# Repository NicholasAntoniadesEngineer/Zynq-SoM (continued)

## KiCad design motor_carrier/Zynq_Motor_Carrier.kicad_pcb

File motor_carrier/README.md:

<!-- schgen:gallery -->
<!-- GENERATED by `schgen gallery` — edits between these markers are overwritten -->
## Generated 3D board views

The placed board rendered from 8 angles by `schgen board` (kicad-cli, the real component 3D models) — regenerated and committed every build, just like the sheets below.

|   |   |   |   |
|---|---|---|---|
| <br>**Perspective (front)** | <br>**Perspective (rear)** | <br>**Top** | <br>**Bottom** |
| <br>**Front edge** | <br>**Back edge** | <br>**Left edge** | <br>**Right edge** |

## Ratsnest views

Placed-board airwires, regenerated by `schgen board`: blue/orange = the subsystem's parts (top/bottom side), steel = SoM, green = intra-subsystem, red = to the SoM. `wired` = in `placement.wired_sheets`.

|   |   |
|---|---|
| <br>**Board (top)** | <br>**Board (bottom)** |
| <br>**SoM region** |   |

|   |   |   |   |
|---|---|---|---|
| <br>**board_control** | <br>**bringup_en** | <br>**can_bus** | <br>**debug_boot** |
| <br>**esc_io** | <br>**esc_power** | <br>**ethernet** | <br>**mechanical** |
| <br>**microsd** | <br>**pd_input** | <br>**power** | <br>**power_mon** |
| <br>**power_som** | <br>**rj45_connector** | <br>**uart_bridge** | <br>**usb_uart_connector** |
| <br>**vbat_supply** |   |   |   |

## Generated schematics

Block diagram and all 21 motor_carrier sheets, regenerated by `schgen board` —
every PNG below passed the netlist, ERC and visual gates.

|   |   |   |
|---|---|---|
| <br>**board_control** | <br>**bringup_en** | <br>**can_bus** |
| <br>**debug_boot** | <br>**esc_io** | <br>**esc_power** |
| <br>**ethernet** | <br>**mechanical** | <br>**microsd** |
| <br>**pd_input** | <br>**power** | <br>**power_mon** |
| <br>**power_som** | <br>**rj45_connector** | <br>**som_decoupling** |
| <br>**som_j1** | <br>**som_j2** | <br>**som_j3** |
| <br>**uart_bridge** | <br>**usb_uart_connector** | <br>**vbat_supply** |

| sheet | description |
|---|---|
| [board_control](renders/board_control.png) | Board control: TCA9535 status expander \| I2C 0x20, rail DIP, user LEDs and button, PUDC strap |
| [bringup_en](renders/bringup_en.png) | Bring-up EN cells: 3x SN74LVC1G08 rail DIP-AND-override |
| [can_bus](renders/can_bus.png) | CAN bus port: TCAN1042HGV transceiver \| switched 120R termination, two daisy-chain connectors |
| [debug_boot](renders/debug_boot.png) | JTAG + SWD headers, boot-request DIP, reset |
| [esc_io](renders/esc_io.png) | 8-channel ESC signal interface \| 5 V PWM/DShot drive, read-back, idle bias, telemetry |
| [esc_power](renders/esc_power.png) | ESC power path: XT60 inlet to outlet \| fuse, reverse/inrush/overcurrent protection, INA237 |
| [ethernet](renders/ethernet.png) | Ethernet: HX5008NL magnetics + Bob-Smith |
| [mechanical](renders/mechanical.png) | Mechanical: M3 mounts + chassis-GND bond (fiducials are PCB-only, emitted by the placer) |
| [microsd](renders/microsd.png) | microSD slot (1.8V SoM <-> 3.3V card, TXS02612) |
| [pd_input](renders/pd_input.png) | Power inlet: USB-C PD 20V/3A + TPS26631 eFuse |
| [power](renders/power.png) | Power: +VIN->+5V->+3V3 bucks + +1V8 LDO, PG LEDs |
| [power_mon](renders/power_mon.png) | Rail telemetry: 2x INA3221 + shunts (I2C 0x40/41) |
| [power_som](renders/power_som.png) | Power: +VIN -> +5V_SOM always-on buck |
| [rj45_connector](renders/rj45_connector.png) | RJ45 8P8C jack (plain, ext. magnetics) |
| [som_decoupling](renders/som_decoupling.png) | SoM power-entry decoupling under the DF40 mezzanine |
| [som_j1](renders/som_j1.png) | SoM J1: power / USB / STM32 / JTAG / SDIO / ETH MDI |
| [som_j2](renders/som_j2.png) | SoM J2: FPGA bank 13/33 IO + VCCO rails |
| [som_j3](renders/som_j3.png) | SoM J3: FPGA bank 33/34/35 IO + VCCO rails |
| [uart_bridge](renders/uart_bridge.png) | UART bridge: CP2102N USB-UART |
| [usb_uart_connector](renders/usb_uart_connector.png) | USB-C UFP console port -> CP2102N |
| [vbat_supply](renders/vbat_supply.png) | Battery logic feed: TPS26631 eFuse \| LM61460 8 V pre-regulator, supply selector |
<!-- /schgen:gallery -->

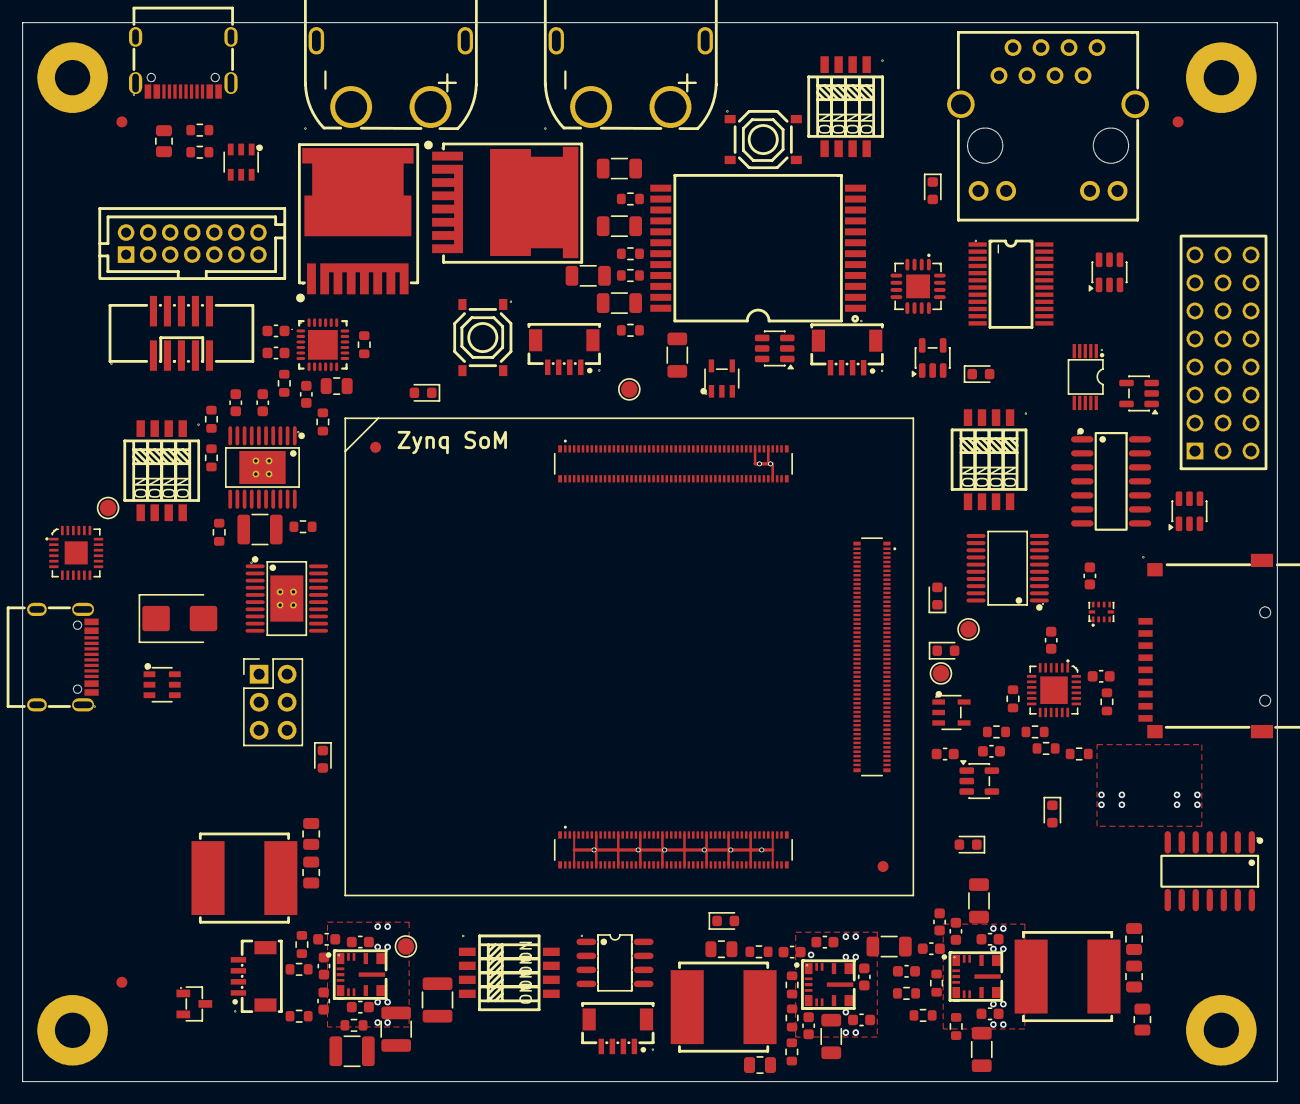
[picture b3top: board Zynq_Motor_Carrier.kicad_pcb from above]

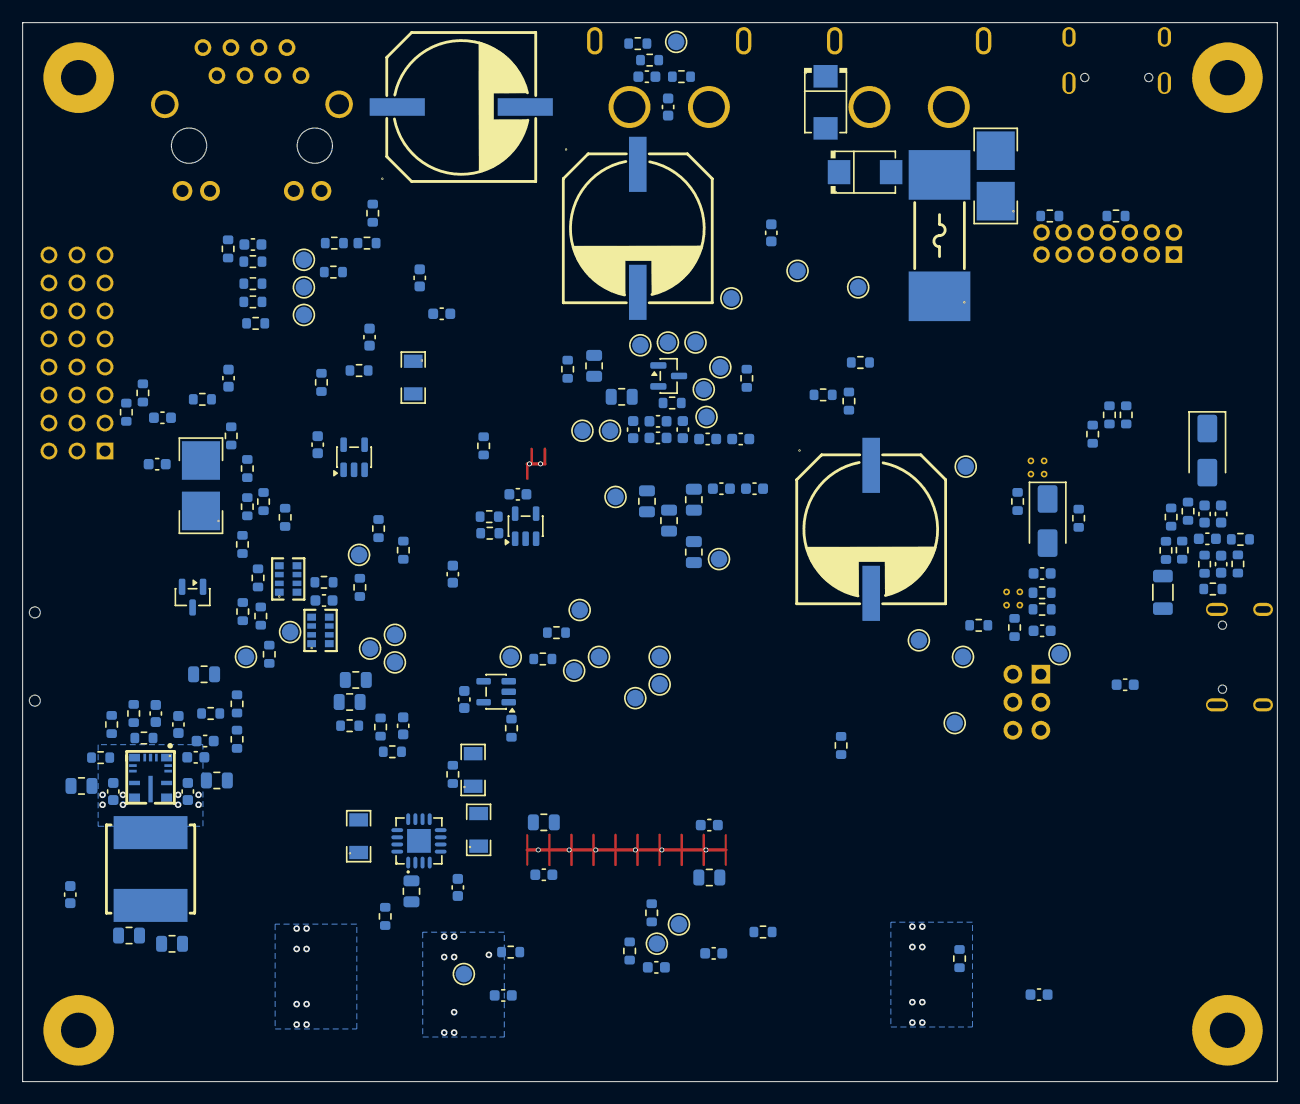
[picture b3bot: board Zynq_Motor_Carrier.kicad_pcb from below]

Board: 6 copper layers, 113.8 x 96.0 mm, 363 parts (204 on the bottom side), 233 nets.

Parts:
C1001, C2001, C2002, C2003, C3001, C3002, C5001, C5004, C5005, C5006, C5007, C6002, C6010, C7006, C9001, C9002, C9004, C10001, C10004, C11001, C11004, C11007, C11009, C11025, C11029, C12001, C12002, C13014, C13017, C13025, C15003, C15004, C15005, C15006, C15009, C15010, C15011, C15012, C15015, C15016, C15017, C15018, C19001, C19003, C19004, C21009: 100n; C_0603_1608Metric
C1002, C1003, C5002, C5003, C12003, C19002, C20001: 10u; C_0805_2012Metric
C6001, C6005, C6006, C6011, C21002, C21005, C21006: 100n/100V; C_0603_1608Metric
C6003, C6004, C21014: 470u; RVT1H471M1213
C6007, C6009, C11012, C11013, C11024, C11028, C11031, C11032, C13022, C13023, C21007, C21008: 1u; C_0603_1608Metric
C6008: 1u/100V; C_1206_3216Metric
C7001, C7002, C7003, C7004, C7005: 1n; C_1206_3216Metric
C9003, C11005, C11006, C11008, C11010, C11011, C11026, C11030, C13018, C13019, C15001, C15002, C15007, C15008, C15013, C15014, C21010, C21011: 22u; C_0805_2012Metric
C10002: 10u; C_1210_3225Metric
C10003, C21001: 47n; C_0603_1608Metric
C11002, C11003, C13015, C13016: 10u; C_1206_3216Metric
C11023, C11027, C13021, C21012: 22p; C_0603_1608Metric
C21003, C21004, C21013: 4u7/100V; C_1210_3225Metric
D1001: green; LED_0603_1608Metric
D1002, D6004, D11001, D11002, D11003, D13004, D21001: red; LED_0603_1608Metric
D3001: NUP2105LT1G
D5001, D5002, D5003: SRV05-4; SOT-23-6
D5004: blue; LED_0603_1608Metric
D6001, D6002: SMBJ28A
D6003, D21002: SS54; D_SMA
D10001: SMBJ22A; D_SMB
F6001: 40A; 0456040.DR
FID1, FID2, FID3, FID4, FID5: Fiducial; Fiducial_1mm_Mask2mm
H8001, H8002, H8003, H8004: MountingHole_M3; MountingHole_3.2mm_M3_Pad
J1001, J3001, J3002, J5002: ZX-SH1.0-4PLT
J4001: 878311420
J4002: HX_JN1.27-2x5; HX_JN1.27-2x5_TP_H4.9
J5001: HX PZ2.54-3x8P ZZ; HX_PZ2.54-3x8P_ZZ
J6001, J6002: XT60PW-M
J9001: TF-01A
J10001, J20001: TYPE-C-31-M-12
J14001: KH-5224-8P8C-D
J16001, J17002, J18003: DF40C-100DP-0.4V(51); HRS_DF40C-100DP-0.4V_51_
J21001: A2541WV-2x3P; PinHeader_2x03_P2.54mm_Vertical
L11001, L11002, L13003, L21001: 10uH; SWPA8040S100MT
Q1001, Q11001: AO3400A; SOT-23
Q6001, Q6002: IPT007N06N
R1001, R1002, R4001, R4002, R6006, R6008: 4k7; R_0603_1608Metric
R1003, R1007, R1012, R3001, R4004, R4005, R4006, R5001, R5004, R5005, R5006, R5007, R5008, R5009, R5010, R5011, R5014, R5015, R6001, R6009, R6010, R6013, R6014, R9006, R11002, R11005, R12001, R21002: 10k; R_0603_1608Metric
R1004, R1009, R1011, R2001, R2002, R2003, R2004, R2005, R2006, R5003, R5012, R6011, R6012, R9001, R9002, R9003, R9004, R9005, R10003, R10006, R11008, R21001, R21005: 100k; R_0603_1608Metric
R1005, R1006, R1008, R1013, R5013, R5016, R11003, R11007, R11012, R11015, R13016, R13019, R19001, R21010, R21011: 1k; R_0603_1608Metric
R1010, R5002, R13015: 13k; R_0603_1608Metric
R3002: 120R; R_0603_1608Metric
R4003, R6004: 100R; R_0603_1608Metric
R6002, R6003, R10005, R20001, R20002, R21003: 5.1k; R_0603_1608Metric
R6005: 49.9R; R_0603_1608Metric
R6007: 15k; R_0603_1608Metric
R7001, R7002, R7003, R7004: 75R; R_0603_1608Metric
R10004, R21004: 5.49k; R_0603_1608Metric
R11001: 40.2k; R_0603_1608Metric
R11004: 23.2k; R_0603_1608Metric
R11006, R11009, R14001, R14002: 330R; R_0603_1608Metric
R11010, R11014, R13018, R21007: 22k; R_0603_1608Metric
R11011, R11013, R13017, R21006: 10R; R_0603_1608Metric
R13014, R19003, R21008: 47k5; R_0603_1608Metric
R19002: 22k1; R_0603_1608Metric
R21009: 6.8k; R_0603_1608Metric
RN5001, RN5002: 4D03WGJ0330T5E
RS6001: 0.5mR; RLM25FEGMR50M
RS12001, RS12002, RS12003: 10mR; RLM12FTCMR010
RS12004: 20mR; RLM12FTCMR020
RT6001: 0.5mR; RLM25FEGMR50M
SW1001, SW3001, SW4001, SW5001: DIP-4; DSHP04TSGER
SW1002: USER; TS-1187A-B-A-B
SW4002: RESET; TS-1187A-B-A-B
T7001: HX5008NLT
TP1001: XP16; TestPoint_Pad_D1.5mm
TP1002: XP17; TestPoint_Pad_D1.5mm
TP1005: STM32_I2C2_SCL; TestPoint_Pad_D1.5mm
TP1006: STM32_I2C2_SDA; TestPoint_Pad_D1.5mm
TP1007: +3V3_SC; TestPoint_Pad_D1.5mm
TP1008: SC_INT_N; TestPoint_Pad_D1.5mm
TP1009: PUDC_34; TestPoint_Pad_D1.5mm
TP1010: +5V_FAN; TestPoint_Pad_D1.5mm
TP1011: ESC_PWR_REQ; TestPoint_Pad_D1.5mm
TP2001: EN_5V0; TestPoint_Pad_D1.5mm
TP2002: EN_3V3; TestPoint_Pad_D1.5mm
TP2003: EN_1V8; TestPoint_Pad_D1.5mm
TP3001: CAN_H; TestPoint_Pad_D1.5mm
TP3002: CAN_L; TestPoint_Pad_D1.5mm
TP4001: VBUS_OUT_EN; TestPoint_Pad_D1.5mm
TP5001: +5V_MOTOR_IO; TestPoint_Pad_D1.5mm
TP5002: ESC_BIAS; TestPoint_Pad_D1.5mm
TP5003: OE_BUF_N; TestPoint_Pad_D1.5mm
TP6001: +VESC_IN; TestPoint_Pad_D1.5mm
TP6002: +VESC; TestPoint_Pad_D1.5mm
TP6003: GND_MOTOR; TestPoint_Pad_D1.5mm
TP6004, TP11004: GND; TestPoint_Pad_D1.5mm
TP6005: +VESC_F; TestPoint_Pad_D1.5mm
TP6006: +VESC_MID; TestPoint_Pad_D1.5mm
TP6007: +VESC_P; TestPoint_Pad_D1.5mm
TP6008: ESC_PWR_EN; TestPoint_Pad_D1.5mm
TP6009: PROT_IMON; TestPoint_Pad_D1.5mm
TP6010: VSENSE_DIV; TestPoint_Pad_D1.5mm
TP9001: SDIO_CMD; TestPoint_Pad_D1.5mm
TP9002: SDIO_CLK; TestPoint_Pad_D1.5mm
TP10001: +VBUS_IN; TestPoint_Pad_D1.5mm
TP10002: +VIN_PD; TestPoint_Pad_D1.5mm
TP11001: +5V; TestPoint_Pad_D1.5mm
TP11002: +3V3; TestPoint_Pad_D1.5mm
TP11003: +1V8; TestPoint_Pad_D1.5mm
TP13001: +5V_SOM; TestPoint_Pad_D1.5mm
TP19001: ZYNQ_PS_UART0_TXD; TestPoint_Pad_D1.5mm
TP19002: ZYNQ_PS_UART0_RXD; TestPoint_Pad_D1.5mm
TP21001: +VBAT_SW; TestPoint_Pad_D1.5mm
TP21002: +VPRE; TestPoint_Pad_D1.5mm
TP21003: +VIN; TestPoint_Pad_D1.5mm
TP21004: +VBAT_D; TestPoint_Pad_D1.5mm
U1001: TCA9535PWR
U1002, U5003: SY6280AAC
U2001, U2002, U2003, U5006, U5007: SN74LVC1G08; SOT-23-5
U3001: TCAN1042HGVDR
U5001: SN74HCT245PWR
U5004, U5005: SN74LVC125ADR
U6001: INA237AIDGSR
U6002: LM74930QRGERQ1
U9001: TXS02612RTWR
U9002: TPD6E001RSER
U10001, U21001: TPS26631PWPR
U10002, U20001: USBLC6-2SC6
U11001, U11002, U13004, U21002: LM61460AANRJRR
U11003: AP2112K-1.8; SOT-23-5
U12001, U12002: INA3221AIRGVR
U19001: CP2102N-A02; CP2102N-A02-GQFN24R

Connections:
+1V8: C9001.1, R11007.1, RS12004.2, TP11003.1, U9001.5, U12002.11
+1V8_REG: C11013.1, RS12004.1, U11003.5, U12002.12
+3V3: C3002.1, C5004.1, C5005.1, C5006.1, C5007.1, C9002.1, C9003.1, C9004.1, C11012.1, C15007.1, C15008.1, C15009.1, C15010.1, C15011.1, C15012.1, C19001.1, C19002.1, C19003.1, C19004.1, D11003.2, J4001.2, J9001.4, J17002.1, J17002.2, J17002.3, J17002.98, J17002.99, J17002.100, J18003.1, J18003.2, J18003.4, J18003.97, J18003.99, R1008.1, R1012.1, R3001.1, R4001.1, R4002.1, R5014.1, R9001.1, R9002.1, R9003.1, R9004.1, R9005.1, R9006.1, R14001.1, R14002.1, R19001.1, RS12003.2, TP11002.1, U3001.5, U5004.14, U5005.14, U5006.2, U5006.5, U5007.2, U5007.5, U9001.17, U9001.21, U9002.10, U11003.1, U12001.1, U19001.5, U19001.6, U19001.7
+3V3_REG: C11010.1, C11011.1, C11023.1, D11002.2, L11002.2, R11004.1, R11013.1, RS12003.1, U12001.2
+3V3_SC: C1001.1, C2001.1, C2002.1, C2003.1, C6002.1, C10004.1, C12001.1, C12002.1, C12003.1, C15013.1, C15014.1, C15015.1, C15016.1, C15017.1, C15018.1, J4002.1, J16001.37, R1001.1, R1002.1, R1003.1, R1005.1, R1006.1, R1007.1, R2002.1, R2004.1, R2006.1, R4003.1, R4004.1, R4005.1, R4006.1, R6001.1, R6010.1, R10006.1, R12001.1, R21005.1, SW1001.5, SW1001.6, SW1001.7, SW1001.8, TP1007.1, U1001.24, U2001.5, U2002.5, U2003.5, U6001.1, U6001.6, U10002.5, U12001.4, U12001.16, U12002.4, U12002.5, U12002.16
+5V: C1002.1, C3001.1, C5001.1, C5002.1, C11007.1, C11008.1, C11029.1, C11030.1, D5001.5, D5002.5, D5003.5, R5001.1, R5016.1, RS12002.2, SW5001.7, TP11001.1, U1002.4, U1002.5, U3001.3, U5001.1, U5001.20, U5003.5, U11002.8, U11002.12, U12001.14
+5V_FAN: C1003.1, J1001.2, TP1010.1, U1002.1
+5V_MOTOR_IO: C5003.1, J5001.9, J5001.10, J5001.11, J5001.12, J5001.13, J5001.14, J5001.15, J5001.16, TP5001.1, U5003.1
+5V_REG: C11005.1, C11006.1, C11026.1, C11027.1, D11001.2, L11001.2, R11001.1, R11011.1, RS12002.1, U12001.15
+5V_SOM: C13018.1, C13019.1, C13021.1, C15001.1, C15002.1, C15003.1, C15004.1, C15005.1, C15006.1, D13004.2, J16001.1, J16001.2, J16001.3, J16001.4, J16001.5, J16001.6, J16001.7, J16001.8, J16001.9, J16001.10, J16001.11, J16001.12, J16001.13, J16001.14, L13003.2, R13014.1, R13017.1, TP13001.1
+VBAT_D: C21002.1, D21002.1, R21001.1, TP21004.1, U21001.1, U21001.2, U21001.3, U21001.6
+VBAT_SW: C21003.1, C21004.1, C21005.1, C21006.1, C21013.1, C21014.1, TP21001.1, U21001.18, U21001.19, U21001.20, U21002.7, U21002.8, U21002.12
+VBUS_IN: C10001.1, D10001.1, J10001.A4B9, J10001.B4A9, R10003.1, TP10001.1, U10001.1, U10001.2, U10001.3, U10001.6, U10001.7
+VESC: C6003.1, C6004.1, C6005.1, D6004.2, J6002.2, R6012.1, RS6001.2, TP6002.1, U6001.8, U6001.9, U6002.19
+VESC_F: C6001.1, D6001.1, D6003.2, D21002.2, F6001.2, Q6001.3, TP6005.1
+VESC_IN: F6001.1, J6001.2, TP6001.1
+VESC_MID: Q6001.2, Q6002.2, TP6006.1, U6002.2, U6002.15
+VESC_P: C6006.1, Q6002.3, R6005.1, R6006.1, RS6001.1, TP6007.1, U6001.10, U6002.24
+VIN: J21001.3, J21001.4, RS12001.1, TP21003.1, U12001.12
+VIN_PD: C10002.1, J21001.1, J21001.2, TP10002.1, U10001.18, U10001.19, U10001.20
+VIN_SYS: C11001.1, C11002.1, C11003.1, C11025.1, C13014.1, C13015.1, C13016.1, C13025.1, RS12001.2, U11001.8, U11001.12, U12001.11, U13004.7, U13004.8, U13004.12
+VPRE: C21010.1, C21011.1, C21012.1, D21001.2, J21001.5, J21001.6, L21001.2, R21006.1, R21008.1, TP21002.1
/board_control/BTN_N: R1007.2, SW1002.1, SW1002.2, U1001.16
/board_control/DIP_USER: R1004.1, SW1001.4, U1001.13
/board_control/FAN_PWM_OD: J1001.4, Q1001.3
/board_control/XP16: TP1001.1, U1001.19
/board_control/XP17: TP1002.1, U1001.20
/can_bus/CAN_H: D3001.1, J3001.2, J3002.2, R3002.1, TP3001.1, U3001.7
/can_bus/CAN_L: D3001.2, J3001.3, J3002.3, SW3001.8, TP3002.1, U3001.6
/can_bus/CAN_TERM: R3002.2, SW3001.1
/esc_io/ESC_BIAS: R5004.2, R5005.2, R5006.2, R5007.2, R5008.2, R5009.2, R5010.2, R5011.2, TP5002.1, U5006.4
/esc_io/ESC_OUT0: D5001.1, J5001.1, R5004.1, RN5001.8
/esc_io/ESC_OUT1: D5001.3, J5001.2, R5005.1, RN5001.7
/esc_io/ESC_OUT2: D5001.4, J5001.3, R5006.1, RN5001.6
/esc_io/ESC_OUT3: D5001.6, J5001.4, R5007.1, RN5001.5
/esc_io/ESC_OUT4: D5002.1, J5001.5, R5008.1, RN5002.8
/esc_io/ESC_OUT5: D5002.3, J5001.6, R5009.1, RN5002.7
/esc_io/ESC_OUT6: D5002.4, J5001.7, R5010.1, RN5002.6
/esc_io/ESC_OUT7: D5002.6, J5001.8, R5011.1, RN5002.5
/esc_io/ESC_SIG0: RN5001.1, U5001.18, U5004.2
/esc_io/ESC_SIG1: RN5001.2, U5001.17, U5004.5
/esc_io/ESC_SIG2: RN5001.3, U5001.16, U5004.9
/esc_io/ESC_SIG3: RN5001.4, U5001.15, U5004.12
/esc_io/ESC_SIG4: RN5002.1, U5001.14, U5005.2
/esc_io/ESC_SIG5: RN5002.2, U5001.13, U5005.5
/esc_io/ESC_SIG6: RN5002.3, U5001.12, U5005.9
/esc_io/ESC_SIG7: RN5002.4, U5001.11, U5005.12
/esc_io/OE_BUF_N: D5004.1, R5001.2, R5015.1, SW5001.8, TP5003.1, U5001.19
/esc_io/SERVO_SW_EN: R5003.1, SW5001.2, U5003.4
/esc_io/TLM_CONN: D5003.1, J5002.2, R5013.1
/esc_power/PROT_DGATE: Q6002.1, U6002.1
/esc_power/PROT_HGATE: Q6001.1, R6004.1, U6002.14
/esc_power/PROT_IMON: R6008.1, R6009.1, TP6009.1, U6002.10
/esc_power/PROT_VS: C6007.2, C6011.1, D6003.1, U6002.4, U6002.7, U6002.22
/esc_power/VSENSE_DIV: C6010.1, R6012.2, R6013.1, R6014.1, TP6010.1
/ethernet/BS_COMMON: C7001.2, C7002.2, C7003.2, C7004.2, C7005.1, R7001.2, R7002.2, R7003.2, R7004.2
/ethernet/ETH_TCT: C7006.1, T7001.1, T7001.4, T7001.7, T7001.10
/ethernet/MCT1: C7001.1, R7001.1, T7001.24
/ethernet/MCT2: C7002.1, R7002.1, T7001.21
/ethernet/MCT3: C7003.1, R7003.1, T7001.18
/ethernet/MCT4: C7004.1, R7004.1, T7001.15
/microsd/SD_CARD_CLK: J9001.5, U9001.19, U9002.1
/microsd/SD_CARD_CMD: J9001.3, R9001.2, U9001.20, U9002.2
/microsd/SD_CARD_D0: J9001.7, R9002.2, U9001.18, U9002.3
/microsd/SD_CARD_D1: J9001.8, R9003.2, U9001.16, U9002.6
/microsd/SD_CARD_D2: J9001.1, R9004.2, U9001.23, U9002.7
/microsd/SD_CARD_D3: J9001.2, R9005.2, U9001.22, U9002.8
/pd_input/PD_USB_DN_CONN: J10001.A7, J10001.B7, U10002.3
/pd_input/PD_USB_DP_CONN: J10001.A6, J10001.B6, U10002.1
/power/BIAS_3V3: C11032.1, R11013.2, U11002.1
/power/BIAS_5V0: C11028.1, R11011.2, U11001.1
/power/RT_3V3: R11014.1, U11002.6
/power/RT_5V0: R11010.1, U11001.6
/power_som/BIAS_5V_SOM: C13023.1, R13017.2, U13004.1
/power_som/RT_5V_SOM: R13018.1, U13004.6
/uart_bridge/CP2102N_VBUS_SNS: R19002.2, R19003.1, U19001.8
/usb_uart_connector/USB_UART_DM_CONN: J20001.A7, J20001.B7, U20001.3
/usb_uart_connector/USB_UART_DP_CONN: J20001.A6, J20001.B6, U20001.1
/vbat_supply/BIAS_PRE: C21008.1, R21006.2, U21002.1
/vbat_supply/RT_PRE: R21007.1, U21002.6
BU_DIP_1V8: R2005.1, SW1001.3, U1001.11, U2003.1
BU_DIP_3V3: R2003.1, SW1001.2, U1001.10, U2002.1
BU_DIP_5V0: R2001.1, SW1001.1, U1001.9, U2001.1
CAN_RX: J17002.54, U3001.4
CAN_TX: J17002.77, R3001.2, U3001.1
CHASSIS_GND: C7005.2, H8001.1, H8002.1, H8003.1, H8004.1, J10001.1, J10001.2, J10001.3, J10001.4, J14001.13, J20001.1, J20001.2, J20001.3, J20001.4
EN_1V8: TP2003.1, U2003.4, U11003.3
EN_3V3: TP2002.1, U2002.4, U11002.7
EN_5V0: TP2001.1, U2001.4, U11001.7
ESC_BUF_OE_N: J17002.57, SW5001.1
ESC_BUF_OE_SENSE_N: R5015.2, U1001.8
ESC_FAULT_N: J17002.37, R6001.2, U1001.7, U6001.3
ESC_FB0: J17002.82, U5004.3
ESC_FB1: J17002.84, U5004.6
ESC_FB2: J17002.78, U5004.8
ESC_FB3: J17002.80, U5004.11
ESC_FB4: J17002.92, U5005.3
ESC_FB5: J17002.94, U5005.6
ESC_FB6: J17002.90, U5005.8
ESC_FB7: J17002.88, U5005.11
ESC_IDLE_SEL: J17002.87, R5012.1, U5006.1
ESC_IMON: J16001.92, R6009.2
ESC_PWM_IN0: J17002.81, U5001.2
ESC_PWM_IN1: J17002.83, U5001.3
ESC_PWM_IN2: J17002.93, U5001.4
ESC_PWM_IN3: J17002.91, U5001.5
ESC_PWM_IN4: J18003.91, U5001.6
ESC_PWM_IN5: J18003.93, U5001.7
ESC_PWM_IN6: J18003.92, U5001.8
ESC_PWM_IN7: J18003.94, U5001.9
ESC_PWR_EN: R6011.1, SW5001.6, TP6008.1, U6002.6
ESC_PWR_FLT_N: R6010.2, U1001.18, U6002.12
ESC_PWR_REQ: R1009.1, SW5001.3, TP1011.1, U1001.17
ESC_TLM_RX: J17002.89, U5007.4
ESC_VBAT_SENSE: J16001.74, R6014.2
ETH_LINE_MDI_0_N: J14001.2, T7001.22
ETH_LINE_MDI_0_P: J14001.1, T7001.23
ETH_LINE_MDI_1_N: J14001.6, T7001.19
ETH_LINE_MDI_1_P: J14001.3, T7001.20
ETH_LINE_MDI_2_N: J14001.5, T7001.16
ETH_LINE_MDI_2_P: J14001.4, T7001.17
ETH_LINE_MDI_3_N: J14001.8, T7001.13
ETH_LINE_MDI_3_P: J14001.7, T7001.14
ETH_PHY_MDI0_N: J16001.95, T7001.3
ETH_PHY_MDI0_P: J16001.97, T7001.2
ETH_PHY_MDI1_N: J16001.89, T7001.6
ETH_PHY_MDI1_P: J16001.91, T7001.5
ETH_PHY_MDI2_N: J16001.83, T7001.9
ETH_PHY_MDI2_P: J16001.85, T7001.8
ETH_PHY_MDI3_N: J16001.77, T7001.12
ETH_PHY_MDI3_P: J16001.79, T7001.11
FAN_PWM: J17002.59, Q1001.1, R1011.1
FAN_TACH: J17002.44, R1012.2, R1013.2
GND: C1001.2, C1002.2, C1003.2, C2001.2, C2002.2, C2003.2, C3001.2, C3002.2, C5001.2, C5002.2, C5003.2, C5004.2, C5005.2, C5006.2, C5007.2, C6002.2, C6010.2, C7006.2, C9001.2, C9002.2, C9003.2, C9004.2, C10001.2, C10002.2, C10003.2, C10004.2, C11001.2, C11002.2, C11003.2, C11005.2, C11006.2, C11007.2, C11008.2, C11010.2, C11011.2, C11012.2, C11013.2, C11024.2, C11025.2, C11026.2, C11028.2, C11029.2, C11030.2, C11031.2, C11032.2, C12001.2, C12002.2, C12003.2, C13014.2, C13015.2, C13016.2, C13018.2, C13019.2, C13022.2, C13023.2, C13025.2, C15001.2, C15002.2, C15003.2, C15004.2, C15005.2, C15006.2, C15007.2, C15008.2, C15009.2, C15010.2, C15011.2, C15012.2, C15013.2, C15014.2, C15015.2, C15016.2, C15017.2, C15018.2, C19001.2, C19002.2, C19003.2, C19004.2, C20001.2, C21001.2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
GND_MOTOR: C6001.2, C6003.2, C6004.2, C6005.2, C6006.2, C6008.2, C6009.2, C6011.2, D3001.3, D5001.2, D5002.2, D5003.2, D6002.1, J3001.4, J3001.5, J3001.6, J3002.4, J3002.5, J3002.6, J5001.17, J5001.18, J5001.19, J5001.20, J5001.21, J5001.22, J5001.23, J5001.24, J5002.1, J5002.5, J5002.6, J6001.1, J6001.3, J6001.4, J6002.1, J6002.3, J6002.4, R6003.2, R6007.2, R6008.2, R6011.2, RT6001.1, TP6003.1, U6002.5, U6002.13, U6002.16
unnamed: C6008.1, R6004.2
unnamed: C11023.2, R11015.1
unnamed: C11027.2, R11012.1
unnamed: C13021.2, R13019.1
unnamed: C21012.2, R21010.1
unnamed: D1001.2, R1005.2
unnamed: D1001.1, U1001.14
unnamed: D1002.2, R1006.2
unnamed: D1002.1, U1001.15
unnamed: D5004.2, R5016.2
unnamed: D6001.2, D6002.2
unnamed: D6004.1, R6002.1
unnamed: D11001.1, R11003.1
unnamed: D11002.1, R11006.1
unnamed: D11003.1, R11009.1
unnamed: D13004.1, R13016.1
unnamed: D21001.1, R21011.1
unnamed: J1001.3, R1013.1
unnamed: J14001.9, R14001.2
unnamed: J14001.11, R14002.2
unnamed: J20001.A5, R20001.1
unnamed: J20001.B5, R20002.1
unnamed: Q11001.3, R11009.2
unnamed: Q11001.1, R11007.2, R11008.1
unnamed: R4003.2, SW4001.8
unnamed: R4006.2, SW4001.4
unnamed: R5013.2, R5014.2, U5007.1
unnamed: R6002.2, R6003.1
unnamed: R1010.1, U1002.3
unnamed: R5002.1, U5003.3
unnamed: C6007.1, U6002.23
unnamed: R6005.2, U6002.20
unnamed: R6007.1, U6002.11
unnamed: R6006.2, U6002.18
unnamed: C6009.1, U6002.9
unnamed: R10005.1, U10001.11
unnamed: R10003.2, R10004.1, U10001.8
unnamed: C10003.1, U10001.10
unnamed: C11004.1, U11001.13, U11001.14
unnamed: R11001.2, R11002.1, R11012.2, U11001.4
unnamed: C11004.2, L11001.1, U11001.10
unnamed: C11024.1, U11001.2
unnamed: C11009.1, U11002.13, U11002.14
unnamed: R11004.2, R11005.1, R11015.2, U11002.4
unnamed: C11009.2, L11002.1, U11002.10
unnamed: C11031.1, U11002.2
unnamed: C13017.1, U13004.13, U13004.14
unnamed: R13014.2, R13015.1, R13019.2, U13004.4
unnamed: C13017.2, L13003.1, U13004.10
unnamed: C13022.1, U13004.2
unnamed: R19001.2, U19001.9
unnamed: R21004.1, U21001.11
unnamed: R21002.2, R21003.1, U21001.8
unnamed: R21001.2, R21002.1, U21001.7
unnamed: C21001.1, U21001.10
unnamed: C21009.1, U21002.13, U21002.14
unnamed: R21008.2, R21009.1, R21010.2, U21002.4
unnamed: C21009.2, L21001.1, U21002.10
unnamed: C21007.1, U21002.2
PD_FLT_N: R10006.2, U1001.4, U10001.15
PMON_ALERT_N: R12001.2, U1001.5, U12001.9, U12002.9
PUDC_34: J18003.39, R1008.2, TP1009.1
SC_INT_N: J16001.41, R1003.2, TP1008.1, U1001.1
SDIO_CLK: J16001.67, TP9002.1, U9001.9
SDIO_CMD: J16001.69, TP9001.1, U9001.4
SDIO_D0: J16001.65, U9001.6
SDIO_D1: J16001.61, U9001.7
SDIO_D2: J16001.73, U9001.1
SDIO_D3: J16001.71, U9001.3
SD_CARD_DETECT: J9001.9, J17002.17, R9006.2
STM32_BOOT0: J16001.57, SW4001.1
STM32_GPIO5: J4002.4, J16001.53
STM32_GPIO6: J4002.2, J16001.45
STM32_GPIO7: J16001.59, R4004.2, SW4001.2
STM32_GPIO8: J16001.54, R4005.2, SW4001.3
STM32_I2C2_SCL: J16001.55, R1001.2, TP1005.1, U1001.22, U6001.5, U12001.6, U12002.6
STM32_I2C2_SDA: J16001.49, R1002.2, TP1006.1, U1001.23, U6001.4, U12001.7, U12002.7
STM32_NRST: J4002.10, J16001.47, SW4002.1, SW4002.2
STM32_RAIL_EN_1V8: J16001.43, R2006.2, U2003.2
STM32_RAIL_EN_3V3: J16001.35, R2004.2, U2002.2
STM32_RAIL_EN_5V0: J16001.33, R2002.2, U2001.2
STM32_USB_CC1: J10001.A5, J16001.29
STM32_USB_CC2: J10001.B5, J16001.31
STM32_USB_D_N: J16001.21, U10002.4
STM32_USB_D_P: J16001.19, U10002.6
USB_UART_DM: U19001.4, U20001.4
USB_UART_DP: U19001.3, U20001.6
USB_UART_VBUS: C20001.1, J20001.A4B9, J20001.B4A9, R19002.1, U20001.5
VBAT_FLT_N: R21005.2, U1001.6, U21001.15
VBUS_OUT_EN: J16001.38, TP4001.1
ZYNQ_PS_UART0_CTS_N: J17002.11, U19001.19
ZYNQ_PS_UART0_RTS_N: J17002.8, U19001.18
ZYNQ_PS_UART0_RXD: J16001.42, TP19002.1, U19001.21
ZYNQ_PS_UART0_TXD: J16001.48, TP19001.1, U19001.20
ZYNQ_TCK: J4001.6, J16001.64
ZYNQ_TDI: J4001.10, J16001.70, R4002.2
ZYNQ_TDO: J4001.8, J16001.68
ZYNQ_TMS: J4001.4, J16001.66, R4001.2

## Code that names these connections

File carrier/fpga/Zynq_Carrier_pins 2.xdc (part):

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##############################################################################

# ---- bank 13 — VCCO = +3V3 (43 pins) --------------------
set_property -dict {PACKAGE_PIN AA9  IOSTANDARD LVCMOS33} [get_ports {DBG_UART_RXD}]  ;# J2.42 IO_L11P_T1_SRCC_13 <- usb_jtag
#   ^ SRCC-capable: # create_clock -name DBG_UART_RXD -period <ns> [get_ports {DBG_UART_RXD}]
set_property -dict {PACKAGE_PIN AA8  IOSTANDARD LVCMOS33} [get_ports {DBG_UART_TXD}]  ;# J2.40 IO_L11N_T1_SRCC_13 <- usb_jtag
set_property -dict {PACKAGE_PIN V10  IOSTANDARD LVCMOS33} [get_ports {ESC_BUF_OE_N}]  ;# J2.57 IO_L1P_T0_13 <- motor_pwm
set_property -dict {PACKAGE_PIN V9   IOSTANDARD LVCMOS33} [get_ports {ESC_FAULT_N}]  ;# J2.37 IO_L1N_T0_13 <- motor_sense
set_property -dict {PACKAGE_PIN U7   IOSTANDARD LVCMOS33} [get_ports {IO_25_13}]  ;# J2.23 IO_25_13 <- user_io
set_property -dict {PACKAGE_PIN Y10  IOSTANDARD LVCMOS33} [get_ports {IO_L10_N_13}]  ;# J2.51 IO_L10N_T1_13 <- pmod
set_property -dict {PACKAGE_PIN Y11  IOSTANDARD LVCMOS33} [get_ports {IO_L10_P_13}]  ;# J2.53 IO_L10P_T1_13 <- pmod
set_property -dict {PACKAGE_PIN AB2  IOSTANDARD LVCMOS33} [get_ports {IO_L15_P_13}]  ;# J2.9 IO_L15P_T2_DQS_13 <- user_io
set_property -dict {PACKAGE_PIN R6   IOSTANDARD LVCMOS33} [get_ports {IO_L19_P_13}]  ;# J2.12 IO_L19P_T3_13 <- user_io
set_property -dict {PACKAGE_PIN V5   IOSTANDARD LVCMOS33} [get_ports {IO_L21_P_13}]  ;# J2.13 IO_L21P_T3_DQS_13 <- user_io
set_property -dict {PACKAGE_PIN U6   IOSTANDARD LVCMOS33} [get_ports {IO_L22_P_13}]  ;# J2.19 IO_L22P_T3_13 <- user_io
set_property -dict {PACKAGE_PIN W5   IOSTANDARD LVCMOS33} [get_ports {IO_L24_N_13}]  ;# J2.7 IO_L24N_T3_13 <- user_io
set_property -dict {PACKAGE_PIN W6   IOSTANDARD LVCMOS33} [get_ports {IO_L24_P_13}]  ;# J2.10 IO_L24P_T3_13 <- user_io
set_property -dict {PACKAGE_PIN W8   IOSTANDARD LVCMOS33} [get_ports {IO_L2_N_13}]  ;# J2.14 IO_L2N_T0_13 <- pmod
set_property -dict {PACKAGE_PIN V8   IOSTANDARD LVCMOS33} [get_ports {IO_L2_P_13}]  ;# J2.20 IO_L2P_T0_13 <- pmod
set_property -dict {PACKAGE_PIN W10  IOSTANDARD LVCMOS33} [get_ports {IO_L3_N_13}]  ;# J2.43 IO_L3N_T0_DQS_13 <- pmod
set_property -dict {PACKAGE_PIN W11  IOSTANDARD LVCMOS33} [get_ports {IO_L3_P_13}]  ;# J2.18 IO_L3P_T0_DQS_13 <- pmod
set_property -dict {PACKAGE_PIN W12  IOSTANDARD LVCMOS33} [get_ports {IO_L4_N_13}]  ;# J2.63 IO_L4N_T0_13 <- pmod
set_property -dict {PACKAGE_PIN V12  IOSTANDARD LVCMOS33} [get_ports {IO_L4_P_13}]  ;# J2.61 IO_L4P_T0_13 <- pmod
set_property -dict {PACKAGE_PIN U12  IOSTANDARD LVCMOS33} [get_ports {IO_L5P_13}]  ;# J2.38 IO_L5P_T0_13 <- pmod
set_property -dict {PACKAGE_PIN U11  IOSTANDARD LVCMOS33} [get_ports {IO_L5_N_13}]  ;# J2.24 IO_L5N_T0_13 <- pmod
set_property -dict {PACKAGE_PIN U10  IOSTANDARD LVCMOS33} [get_ports {IO_L6_P_13}]  ;# J2.21 IO_L6P_T0_13 <- user_io
set_property -dict {PACKAGE_PIN AB12 IOSTANDARD LVCMOS33} [get_ports {IO_L7_N_13}]  ;# J2.64 IO_L7N_T1_13 <- pmod
set_property -dict {PACKAGE_PIN AA12 IOSTANDARD LVCMOS33} [get_ports {IO_L7_P_13}]  ;# J2.62 IO_L7P_T1_13 <- pmod
set_property -dict {PACKAGE_PIN AB11 IOSTANDARD LVCMOS33} [get_ports {IO_L8_N_13}]  ;# J2.60 IO_L8N_T1_13 <- pmod
set_property -dict {PACKAGE_PIN AA11 IOSTANDARD LVCMOS33} [get_ports {IO_L8_P_13}]  ;# J2.58 IO_L8P_T1_13 <- pmod
set_property -dict {PACKAGE_PIN AB9  IOSTANDARD LVCMOS33} [get_ports {IO_L9_DQS_N_13}]  ;# J2.48 IO_L9N_T1_DQS_13 <- pmod
set_property -dict {PACKAGE_PIN AB10 IOSTANDARD LVCMOS33} [get_ports {IO_L9_DQS_P_13}]  ;# J2.50 IO_L9P_T1_DQS_13 <- pmod
set_property -dict {PACKAGE_PIN AB6  IOSTANDARD LVCMOS33} [get_ports {LCD_CTP_INT}]  ;# J2.32 IO_L17N_T2_13 <- lcd
set_property -dict {PACKAGE_PIN AB7  IOSTANDARD LVCMOS33} [get_ports {LCD_CTP_RST}]  ;# J2.34 IO_L17P_T2_13 <- lcd
set_property -dict {PACKAGE_PIN AB4  IOSTANDARD LVCMOS33} [get_ports {LCD_CTP_SCL}]  ;# J2.28 IO_L16N_T2_13 <- lcd
set_property -dict {PACKAGE_PIN AB5  IOSTANDARD LVCMOS33} [get_ports {LCD_CTP_SDA}]  ;# J2.30 IO_L16P_T2_13 <- lcd
set_property -dict {PACKAGE_PIN Y6   IOSTANDARD LVCMOS33} [get_ports {PMODX_IO1}]  ;# J2.29 IO_L13P_T2_MRCC_13 <- pmod_expansion
#   ^ MRCC-capable: # create_clock -name PMODX_IO1 -period <ns> [get_ports {PMODX_IO1}]
set_property -dict {PACKAGE_PIN Y5   IOSTANDARD LVCMOS33} [get_ports {PMODX_IO2}]  ;# J2.27 IO_L13N_T2_MRCC_13 <- pmod_expansion
set_property -dict {PACKAGE_PIN V7   IOSTANDARD LVCMOS33} [get_ports {PMODX_IO3}]  ;# J2.33 IO_L23P_T3_13 <- pmod_expansion
set_property -dict {PACKAGE_PIN W7   IOSTANDARD LVCMOS33} [get_ports {PMODX_IO4}]  ;# J2.31 IO_L23N_T3_13 <- pmod_expansion
set_property -dict {PACKAGE_PIN AA7  IOSTANDARD LVCMOS33} [get_ports {PMODX_IO5}]  ;# J2.41 IO_L14P_T2_SRCC_13 <- pmod_expansion
#   ^ SRCC-capable: # create_clock -name PMODX_IO5 -period <ns> [get_ports {PMODX_IO5}]
set_property -dict {PACKAGE_PIN AA6  IOSTANDARD LVCMOS33} [get_ports {PMODX_IO6}]  ;# J2.39 IO_L14N_T2_SRCC_13 <- pmod_expansion
set_property -dict {PACKAGE_PIN Y9   IOSTANDARD LVCMOS33} [get_ports {PMODX_IO7}]  ;# J2.49 IO_L12P_T1_MRCC_13 <- pmod_expansion
#   ^ MRCC-capable: # create_clock -name PMODX_IO7 -period <ns> [get_ports {PMODX_IO7}]
set_property -dict {PACKAGE_PIN Y8   IOSTANDARD LVCMOS33} [get_ports {PMODX_IO8}]  ;# J2.47 IO_L12N_T1_MRCC_13 <- pmod_expansion
set_property -dict {PACKAGE_PIN U9   IOSTANDARD LVCMOS33} [get_ports {SD_CARD_DETECT}]  ;# J2.17 IO_L6N_T0_VREF_13 <- microsd
set_property -dict {PACKAGE_PIN Y4   IOSTANDARD LVCMOS33} [get_ports {ZYNQ_PS_UART0_CTS_N}]  ;# J2.11 IO_L18P_T2_13 <- uart_bridge
set_property -dict {PACKAGE_PIN AA4  IOSTANDARD LVCMOS33} [get_ports {ZYNQ_PS_UART0_RTS_N}]  ;# J2.8 IO_L18N_T2_13 <- uart_bridge

# ---- bank 33 — VCCO = +3V3 (39 pins) --------------------
set_property -dict {PACKAGE_PIN T22  IOSTANDARD LVCMOS33} [get_ports {CAM_EN}]  ;# J3.85 IO_L2P_T0_33 <- camera
set_property -dict {PACKAGE_PIN U22  IOSTANDARD LVCMOS33} [get_ports {CAM_LED}]  ;# J3.87 IO_L2N_T0_33 <- camera
set_property -dict {PACKAGE_PIN T21  IOSTANDARD LVCMOS33} [get_ports {CAM_SCL}]  ;# J3.86 IO_L1P_T0_33 <- camera
set_property -dict {PACKAGE_PIN U21  IOSTANDARD LVCMOS33} [get_ports {CAM_SDA}]  ;# J3.89 IO_L1N_T0_33 <- camera
set_property -dict {PACKAGE_PIN W16  IOSTANDARD LVCMOS33} [get_ports {ESC_PWM_IN0}]  ;# J2.81 IO_L14P_T2_SRCC_33 <- motor_pwm
#   ^ SRCC-capable: # create_clock -name ESC_PWM_IN0 -period <ns> [get_ports {ESC_PWM_IN0}]
set_property -dict {PACKAGE_PIN Y16  IOSTANDARD LVCMOS33} [get_ports {ESC_PWM_IN1}]  ;# J2.83 IO_L14N_T2_SRCC_33 <- motor_pwm
set_property -dict {PACKAGE_PIN Y19  IOSTANDARD LVCMOS33} [get_ports {ESC_PWM_IN2}]  ;# J2.93 IO_L11P_T1_SRCC_33 <- motor_pwm
#   ^ SRCC-capable: # create_clock -name ESC_PWM_IN2 -period <ns> [get_ports {ESC_PWM_IN2}]
set_property -dict {PACKAGE_PIN AA19 IOSTANDARD LVCMOS33} [get_ports {ESC_PWM_IN3}]  ;# J2.91 IO_L11N_T1_SRCC_33 <- motor_pwm
set_property -dict {PACKAGE_PIN V22  IOSTANDARD LVCMOS33} [get_ports {ESC_PWM_IN4}]  ;# J3.91 IO_L3P_T0_DQS_33 <- motor_pwm
set_property -dict {PACKAGE_PIN W22  IOSTANDARD LVCMOS33} [get_ports {ESC_PWM_IN5}]  ;# J3.93 IO_L3N_T0_DQS_33 <- motor_pwm
set_property -dict {PACKAGE_PIN U20  IOSTANDARD LVCMOS33} [get_ports {ESC_PWM_IN6}]  ;# J3.92 IO_L5P_T0_33 <- motor_pwm
set_property -dict {PACKAGE_PIN V20  IOSTANDARD LVCMOS33} [get_ports {ESC_PWM_IN7}]  ;# J3.94 IO_L5N_T0_33 <- motor_pwm
set_property -dict {PACKAGE_PIN W13  IOSTANDARD LVCMOS33} [get_ports {HDMI_RX_5V_DET}]  ;# J2.44 IO_L20N_T3_33 <- hdmi_rx
set_property -dict {PACKAGE_PIN V13  IOSTANDARD LVCMOS33} [get_ports {HDMI_RX_CEC}]  ;# J2.59 IO_L20P_T3_33 <- hdmi_rx
# tmds_pair (100R): HDMI_RX_CLK_P / HDMI_RX_CLK_N
set_property -dict {PACKAGE_PIN Y18  IOSTANDARD TMDS_33} [get_ports {HDMI_RX_CLK_P}]  ;# J2.90 IO_L12P_T1_MRCC_33 <- hdmi_rx, hdmi_rx_term
#   ^ MRCC-capable: # create_clock -name HDMI_RX_CLK_P -period <ns> [get_ports {HDMI_RX_CLK_P}]
set_property -dict {PACKAGE_PIN AA18 IOSTANDARD TMDS_33} [get_ports {HDMI_RX_CLK_N}]  ;# J2.88 IO_L12N_T1_MRCC_33 <- hdmi_rx, hdmi_rx_term
# tmds_pair (100R): HDMI_RX_D0_P / HDMI_RX_D0_N
set_property -dict {PACKAGE_PIN AB19 IOSTANDARD TMDS_33} [get_ports {HDMI_RX_D0_P}]  ;# J2.92 IO_L10P_T1_33 <- hdmi_rx, hdmi_rx_term
set_property -dict {PACKAGE_PIN AB20 IOSTANDARD TMDS_33} [get_ports {HDMI_RX_D0_N}]  ;# J2.94 IO_L10N_T1_33 <- hdmi_rx, hdmi_rx_term
# tmds_pair (100R): HDMI_RX_D1_P / HDMI_RX_D1_N
set_property -dict {PACKAGE_PIN AA17 IOSTANDARD TMDS_33} [get_ports {HDMI_RX_D1_P}]  ;# J2.82 IO_L17P_T2_33 <- hdmi_rx, hdmi_rx_term
set_property -dict {PACKAGE_PIN AB17 IOSTANDARD TMDS_33} [get_ports {HDMI_RX_D1_N}]  ;# J2.84 IO_L17N_T2_33 <- hdmi_rx, hdmi_rx_term
# tmds_pair (100R): HDMI_RX_D2_P / HDMI_RX_D2_N
set_property -dict {PACKAGE_PIN AA16 IOSTANDARD TMDS_33} [get_ports {HDMI_RX_D2_P}]  ;# J2.78 IO_L18P_T2_33 <- hdmi_rx, hdmi_rx_term
set_property -dict {PACKAGE_PIN AB16 IOSTANDARD TMDS_33} [get_ports {HDMI_RX_D2_N}]  ;# J2.80 IO_L18N_T2_33 <- hdmi_rx, hdmi_rx_term
set_property -dict {PACKAGE_PIN V18  IOSTANDARD LVCMOS33} [get_ports {IO_L6_P_33}]  ;# J2.89 IO_L6P_T0_33 <- unclaimed (wave-3 function map)
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
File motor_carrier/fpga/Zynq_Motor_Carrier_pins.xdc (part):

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##############################################################################

# ---- bank 13 — VCCO = +3V3 (43 pins) --------------------
set_property -dict {PACKAGE_PIN V10  IOSTANDARD LVCMOS33} [get_ports {ESC_BUF_OE_N}]  ;# J2.57 IO_L1P_T0_13 <- esc_io
set_property -dict {PACKAGE_PIN V9   IOSTANDARD LVCMOS33} [get_ports {ESC_FAULT_N}]  ;# J2.37 IO_L1N_T0_13 <- board_control, esc_power
set_property -dict {PACKAGE_PIN U7   IOSTANDARD LVCMOS33} [get_ports {IO_25_13}]  ;# J2.23 IO_25_13 <- unclaimed (wave-3 function map)
set_property -dict {PACKAGE_PIN Y10  IOSTANDARD LVCMOS33} [get_ports {IO_L10_N_13}]  ;# J2.51 IO_L10N_T1_13 <- unclaimed (wave-3 function map)
set_property -dict {PACKAGE_PIN Y11  IOSTANDARD LVCMOS33} [get_ports {IO_L10_P_13}]  ;# J2.53 IO_L10P_T1_13 <- unclaimed (wave-3 function map)
set_property -dict {PACKAGE_PIN AA8  IOSTANDARD LVCMOS33} [get_ports {IO_L11_SRCC_N_13}]  ;# J2.40 IO_L11N_T1_SRCC_13 <- unclaimed (wave-3 function map)
set_property -dict {PACKAGE_PIN AA9  IOSTANDARD LVCMOS33} [get_ports {IO_L11_SRCC_P_13}]  ;# J2.42 IO_L11P_T1_SRCC_13 <- unclaimed (wave-3 function map)
#   ^ SRCC-capable: # create_clock -name IO_L11_SRCC_P_13 -period <ns> [get_ports {IO_L11_SRCC_P_13}]
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set_property -dict {PACKAGE_PIN AA6  IOSTANDARD LVCMOS33} [get_ports {IO_L14_N_SRCC_13}]  ;# J2.39 IO_L14N_T2_SRCC_13 <- unclaimed (wave-3 function map)
set_property -dict {PACKAGE_PIN AA7  IOSTANDARD LVCMOS33} [get_ports {IO_L14_P_SRCC_13}]  ;# J2.41 IO_L14P_T2_SRCC_13 <- unclaimed (wave-3 function map)
#   ^ SRCC-capable: # create_clock -name IO_L14_P_SRCC_13 -period <ns> [get_ports {IO_L14_P_SRCC_13}]
set_property -dict {PACKAGE_PIN AB2  IOSTANDARD LVCMOS33} [get_ports {IO_L15_P_13}]  ;# J2.9 IO_L15P_T2_DQS_13 <- unclaimed (wave-3 function map)
set_property -dict {PACKAGE_PIN AB4  IOSTANDARD LVCMOS33} [get_ports {IO_L16_N_13}]  ;# J2.28 IO_L16N_T2_13 <- unclaimed (wave-3 function map)
set_property -dict {PACKAGE_PIN AB5  IOSTANDARD LVCMOS33} [get_ports {IO_L16_P_13}]  ;# J2.30 IO_L16P_T2_13 <- unclaimed (wave-3 function map)
set_property -dict {PACKAGE_PIN AB6  IOSTANDARD LVCMOS33} [get_ports {IO_L17_N_13}]  ;# J2.32 IO_L17N_T2_13 <- unclaimed (wave-3 function map)
set_property -dict {PACKAGE_PIN AB7  IOSTANDARD LVCMOS33} [get_ports {IO_L17_P_13}]  ;# J2.34 IO_L17P_T2_13 <- unclaimed (wave-3 function map)
set_property -dict {PACKAGE_PIN R6   IOSTANDARD LVCMOS33} [get_ports {IO_L19_P_13}]  ;# J2.12 IO_L19P_T3_13 <- unclaimed (wave-3 function map)
set_property -dict {PACKAGE_PIN V5   IOSTANDARD LVCMOS33} [get_ports {IO_L21_P_13}]  ;# J2.13 IO_L21P_T3_DQS_13 <- unclaimed (wave-3 function map)
set_property -dict {PACKAGE_PIN U6   IOSTANDARD LVCMOS33} [get_ports {IO_L22_P_13}]  ;# J2.19 IO_L22P_T3_13 <- unclaimed (wave-3 function map)
set_property -dict {PACKAGE_PIN W7   IOSTANDARD LVCMOS33} [get_ports {IO_L23_N_13}]  ;# J2.31 IO_L23N_T3_13 <- unclaimed (wave-3 function map)
set_property -dict {PACKAGE_PIN V7   IOSTANDARD LVCMOS33} [get_ports {IO_L23_P_13}]  ;# J2.33 IO_L23P_T3_13 <- unclaimed (wave-3 function map)
set_property -dict {PACKAGE_PIN W5   IOSTANDARD LVCMOS33} [get_ports {IO_L24_N_13}]  ;# J2.7 IO_L24N_T3_13 <- unclaimed (wave-3 function map)
set_property -dict {PACKAGE_PIN W6   IOSTANDARD LVCMOS33} [get_ports {IO_L24_P_13}]  ;# J2.10 IO_L24P_T3_13 <- unclaimed (wave-3 function map)
set_property -dict {PACKAGE_PIN W8   IOSTANDARD LVCMOS33} [get_ports {IO_L2_N_13}]  ;# J2.14 IO_L2N_T0_13 <- unclaimed (wave-3 function map)
set_property -dict {PACKAGE_PIN V8   IOSTANDARD LVCMOS33} [get_ports {IO_L2_P_13}]  ;# J2.20 IO_L2P_T0_13 <- unclaimed (wave-3 function map)
set_property -dict {PACKAGE_PIN W10  IOSTANDARD LVCMOS33} [get_ports {IO_L3_N_13}]  ;# J2.43 IO_L3N_T0_DQS_13 <- unclaimed (wave-3 function map)
set_property -dict {PACKAGE_PIN W11  IOSTANDARD LVCMOS33} [get_ports {IO_L3_P_13}]  ;# J2.18 IO_L3P_T0_DQS_13 <- unclaimed (wave-3 function map)
set_property -dict {PACKAGE_PIN W12  IOSTANDARD LVCMOS33} [get_ports {IO_L4_N_13}]  ;# J2.63 IO_L4N_T0_13 <- unclaimed (wave-3 function map)
set_property -dict {PACKAGE_PIN V12  IOSTANDARD LVCMOS33} [get_ports {IO_L4_P_13}]  ;# J2.61 IO_L4P_T0_13 <- unclaimed (wave-3 function map)
set_property -dict {PACKAGE_PIN U12  IOSTANDARD LVCMOS33} [get_ports {IO_L5P_13}]  ;# J2.38 IO_L5P_T0_13 <- unclaimed (wave-3 function map)
set_property -dict {PACKAGE_PIN U11  IOSTANDARD LVCMOS33} [get_ports {IO_L5_N_13}]  ;# J2.24 IO_L5N_T0_13 <- unclaimed (wave-3 function map)
set_property -dict {PACKAGE_PIN U10  IOSTANDARD LVCMOS33} [get_ports {IO_L6_P_13}]  ;# J2.21 IO_L6P_T0_13 <- unclaimed (wave-3 function map)
set_property -dict {PACKAGE_PIN AB12 IOSTANDARD LVCMOS33} [get_ports {IO_L7_N_13}]  ;# J2.64 IO_L7N_T1_13 <- unclaimed (wave-3 function map)
set_property -dict {PACKAGE_PIN AA12 IOSTANDARD LVCMOS33} [get_ports {IO_L7_P_13}]  ;# J2.62 IO_L7P_T1_13 <- unclaimed (wave-3 function map)
set_property -dict {PACKAGE_PIN AB11 IOSTANDARD LVCMOS33} [get_ports {IO_L8_N_13}]  ;# J2.60 IO_L8N_T1_13 <- unclaimed (wave-3 function map)
set_property -dict {PACKAGE_PIN AA11 IOSTANDARD LVCMOS33} [get_ports {IO_L8_P_13}]  ;# J2.58 IO_L8P_T1_13 <- unclaimed (wave-3 function map)
set_property -dict {PACKAGE_PIN AB9  IOSTANDARD LVCMOS33} [get_ports {IO_L9_DQS_N_13}]  ;# J2.48 IO_L9N_T1_DQS_13 <- unclaimed (wave-3 function map)
set_property -dict {PACKAGE_PIN AB10 IOSTANDARD LVCMOS33} [get_ports {IO_L9_DQS_P_13}]  ;# J2.50 IO_L9P_T1_DQS_13 <- unclaimed (wave-3 function map)
set_property -dict {PACKAGE_PIN U9   IOSTANDARD LVCMOS33} [get_ports {SD_CARD_DETECT}]  ;# J2.17 IO_L6N_T0_VREF_13 <- microsd
set_property -dict {PACKAGE_PIN Y4   IOSTANDARD LVCMOS33} [get_ports {ZYNQ_PS_UART0_CTS_N}]  ;# J2.11 IO_L18P_T2_13 <- uart_bridge
set_property -dict {PACKAGE_PIN AA4  IOSTANDARD LVCMOS33} [get_ports {ZYNQ_PS_UART0_RTS_N}]  ;# J2.8 IO_L18N_T2_13 <- uart_bridge

# ---- bank 33 — VCCO = +3V3 (39 pins) --------------------
set_property -dict {PACKAGE_PIN U16  IOSTANDARD LVCMOS33} [get_ports {CAN_RX}]  ;# J2.54 IO_L15N_T2_DQS_33 <- can_bus
set_property -dict {PACKAGE_PIN V15  IOSTANDARD LVCMOS33} [get_ports {CAN_TX}]  ;# J2.77 IO_L19N_T3_VREF_33 <- can_bus
set_property -dict {PACKAGE_PIN AA17 IOSTANDARD LVCMOS33} [get_ports {ESC_FB0}]  ;# J2.82 IO_L17P_T2_33 <- esc_io
set_property -dict {PACKAGE_PIN AB17 IOSTANDARD LVCMOS33} [get_ports {ESC_FB1}]  ;# J2.84 IO_L17N_T2_33 <- esc_io
set_property -dict {PACKAGE_PIN AA16 IOSTANDARD LVCMOS33} [get_ports {ESC_FB2}]  ;# J2.78 IO_L18P_T2_33 <- esc_io
set_property -dict {PACKAGE_PIN AB16 IOSTANDARD LVCMOS33} [get_ports {ESC_FB3}]  ;# J2.80 IO_L18N_T2_33 <- esc_io
set_property -dict {PACKAGE_PIN AB19 IOSTANDARD LVCMOS33} [get_ports {ESC_FB4}]  ;# J2.92 IO_L10P_T1_33 <- esc_io
set_property -dict {PACKAGE_PIN AB20 IOSTANDARD LVCMOS33} [get_ports {ESC_FB5}]  ;# J2.94 IO_L10N_T1_33 <- esc_io
set_property -dict {PACKAGE_PIN Y18  IOSTANDARD LVCMOS33} [get_ports {ESC_FB6}]  ;# J2.90 IO_L12P_T1_MRCC_33 <- esc_io
#   ^ MRCC-capable: # create_clock -name ESC_FB6 -period <ns> [get_ports {ESC_FB6}]
set_property -dict {PACKAGE_PIN AA18 IOSTANDARD LVCMOS33} [get_ports {ESC_FB7}]  ;# J2.88 IO_L12N_T1_MRCC_33 <- esc_io
set_property -dict {PACKAGE_PIN V17  IOSTANDARD LVCMOS33} [get_ports {ESC_IDLE_SEL}]  ;# J2.87 IO_L16N_T2_33 <- esc_io
set_property -dict {PACKAGE_PIN W16  IOSTANDARD LVCMOS33} [get_ports {ESC_PWM_IN0}]  ;# J2.81 IO_L14P_T2_SRCC_33 <- esc_io
#   ^ SRCC-capable: # create_clock -name ESC_PWM_IN0 -period <ns> [get_ports {ESC_PWM_IN0}]
set_property -dict {PACKAGE_PIN Y16  IOSTANDARD LVCMOS33} [get_ports {ESC_PWM_IN1}]  ;# J2.83 IO_L14N_T2_SRCC_33 <- esc_io
set_property -dict {PACKAGE_PIN Y19  IOSTANDARD LVCMOS33} [get_ports {ESC_PWM_IN2}]  ;# J2.93 IO_L11P_T1_SRCC_33 <- esc_io
#   ^ SRCC-capable: # create_clock -name ESC_PWM_IN2 -period <ns> [get_ports {ESC_PWM_IN2}]
set_property -dict {PACKAGE_PIN AA19 IOSTANDARD LVCMOS33} [get_ports {ESC_PWM_IN3}]  ;# J2.91 IO_L11N_T1_SRCC_33 <- esc_io
set_property -dict {PACKAGE_PIN V22  IOSTANDARD LVCMOS33} [get_ports {ESC_PWM_IN4}]  ;# J3.91 IO_L3P_T0_DQS_33 <- esc_io
set_property -dict {PACKAGE_PIN W22  IOSTANDARD LVCMOS33} [get_ports {ESC_PWM_IN5}]  ;# J3.93 IO_L3N_T0_DQS_33 <- esc_io
set_property -dict {PACKAGE_PIN U20  IOSTANDARD LVCMOS33} [get_ports {ESC_PWM_IN6}]  ;# J3.92 IO_L5P_T0_33 <- esc_io
set_property -dict {PACKAGE_PIN V20  IOSTANDARD LVCMOS33} [get_ports {ESC_PWM_IN7}]  ;# J3.94 IO_L5N_T0_33 <- esc_io
set_property -dict {PACKAGE_PIN V18  IOSTANDARD LVCMOS33} [get_ports {ESC_TLM_RX}]  ;# J2.89 IO_L6P_T0_33 <- esc_io
set_property -dict {PACKAGE_PIN V13  IOSTANDARD LVCMOS33} [get_ports {FAN_PWM}]  ;# J2.59 IO_L20P_T3_33 <- board_control
set_property -dict {PACKAGE_PIN W13  IOSTANDARD LVCMOS33} [get_ports {FAN_TACH}]  ;# J2.44 IO_L20N_T3_33 <- board_control
set_property -dict {PACKAGE_PIN U14  IOSTANDARD LVCMOS33} [get_ports {IO_25_33}]  ;# J2.79 IO_25_33 <- unclaimed (wave-3 function map)
set_property -dict {PACKAGE_PIN V14  IOSTANDARD LVCMOS33} [get_ports {IO_L19_P_33}]  ;# J2.22 IO_L19P_T3_33 <- unclaimed (wave-3 function map)
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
